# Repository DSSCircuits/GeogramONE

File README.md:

The Geogram ONE is an open source tracking device/development board based off the Arduino platform.

The hardware design and software files are released under CC-SA v3 license.

There are several attributable portions of code that will be listed shortly.

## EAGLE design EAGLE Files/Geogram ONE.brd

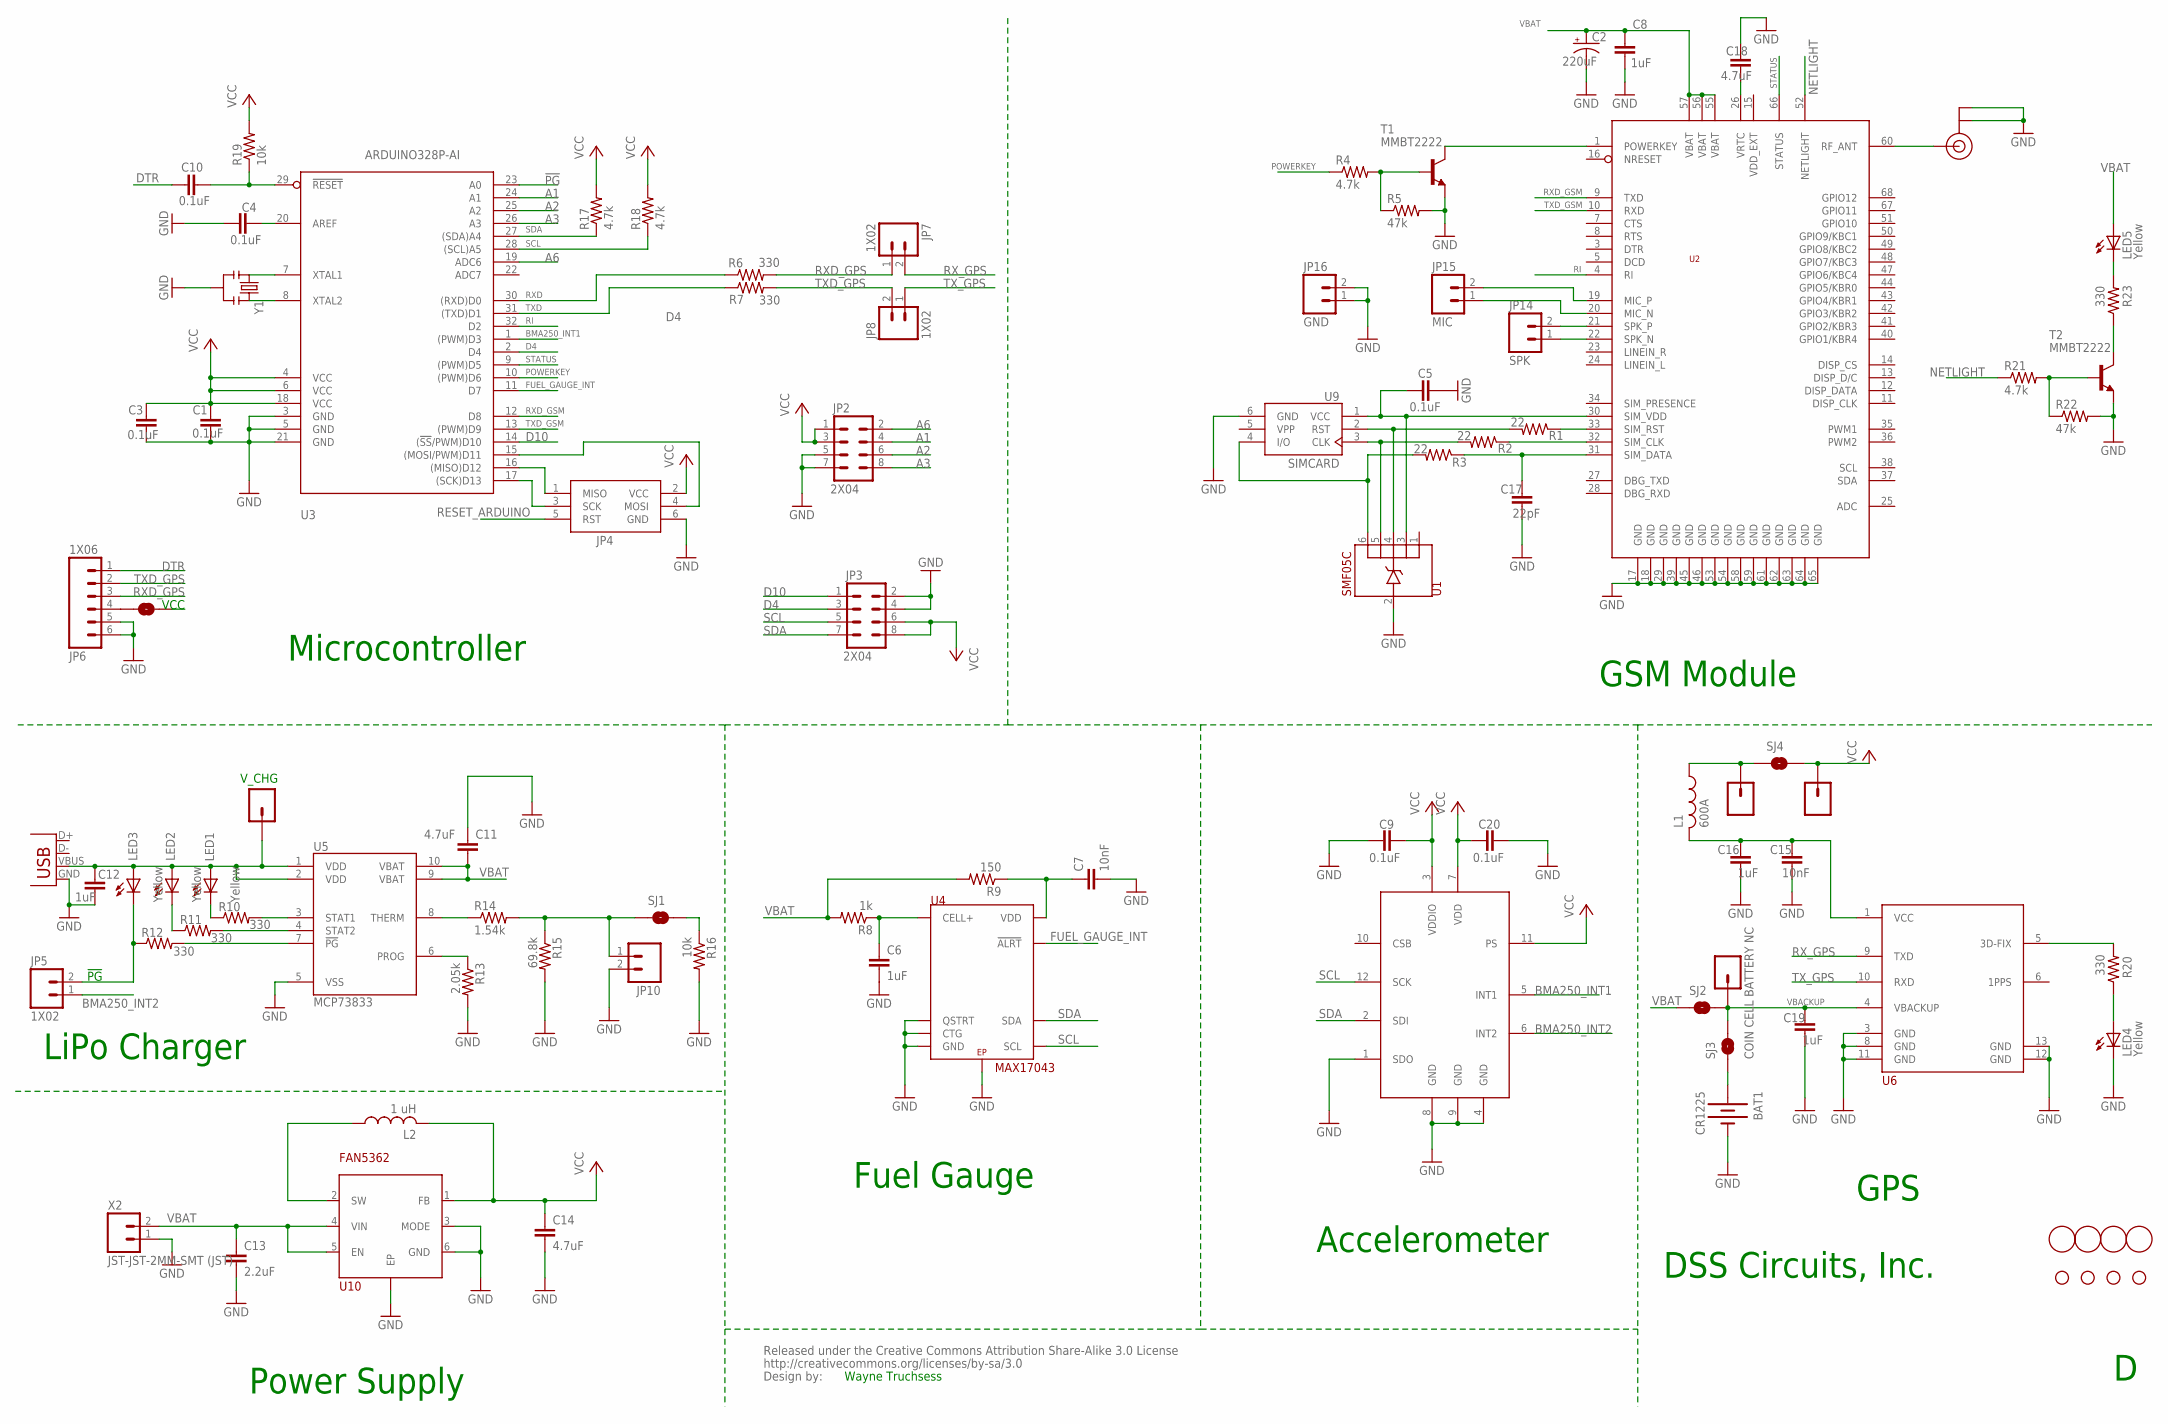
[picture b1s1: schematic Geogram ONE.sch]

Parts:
BAT1: CR1225; BATTCON_12MM; MOUSER# 534-3000TR; DIGIKEY# 3000KTR-ND
C1, C3, C4, C5, C9, C10, C20: 0.1uF; C0603; MOUSER# 80-C0603C104K8R; DIGIKEY# 399-1095-2-ND
C2: 220uF; D/7343-31R; MOUSER# 80-T520D227M010; DIGIKEY# 399-4045-2-ND
C6, C8, C12, C16, C19: 1uF; C0603; MOUSER# 810-C1608X5R1A105K; DIGIKEY# 445-1321-2-ND
C7, C15: 10nF; C0603; MOUSER# 77-VJ0603Y103KXQCBC
C11, C14, C18: 4.7uF; C0603; MOUSER# 80-C0603C475K9P; DIGIKEY# 399-3482-2-ND
C13: 2.2uF; C0603; MOUSER# 80-C0603C225K9P; DIGIKEY# 399-3362-2-ND
C17: 22pF; C0603; MOUSER# 77-VJ0603A220KXJPBC
FIDUCIAL1, FIDUCIAL2, FIDUCIAL3, FIDUCIAL4: FIDUCIAL; FIDUCIAL_1MM
JP2, JP3: 2X04; 2X4
JP4: AVRISP-6; AVRISP
JP5, JP7, JP8: 1X02; 1X02_NO_SILK
JP6: 1X06
JP9: V_CHG; 1X01
JP10: EXT THERMISTER; 1X02_NO_SILK
JP11: EXT_BAT; 1X01
JP12, JP13: EXT GPS POWER JPR; 1X01
JP14: SPK; 1X02_NO_SILK
JP15: MIC; 1X02_NO_SILK
JP16: GND; 1X02_NO_SILK
L1: 600A; L2012C; MOUSER# 810-MMZ2012R601A
L2: 1 uH; L2012C; MOUSER# 81-LQM21PN1R0MC0D; DIGIKEY# 490-4992-2-ND
LED1, LED2, LED3, LED4, LED5: Yellow; CHIP-LED0603; MOUSER# 720-LYQ971H1K136; DIGIKEY# 475-2557-2-ND
LICENSE: CREATIVE_COMMONS
R1, R2, R3: 22; R0603; MOUSER# 667-ERJ-3EKF22R0V; DIGIKEY# P22.0HTR-ND
R4, R17, R18, R21: 4.7k; R0603; MOUSER# 667-ERJ-3EKF4701V; DIGIKEY# P4.70KHTR-ND
R5, R22: 47k; R0603; MOUSER# 667-ERJ-3EKF4702V; DIGIKEY# P47.0KHTR-ND
R6, R7, R10, R11, R12, R20, R23: 330; R0603; MOUSER# 667-ERJ-3EKF3300V; DIGIKEY# P330HTR-ND
R8: 1k; R0603; MOUSER# 667-ERJ-3EKF1001V; DIGIKEY# P1.00KHTR-ND
R9: 150; R0603; MOUSER# 667-ERJ-3EKF1500V; DIGIKEY# P150HTR-ND
R13: 2.05k; R0603; MOUSER# 667-ERJ-3EKF2051V; DIGIKEY# P2.05KHTR-ND
R14: 1.54k; R0603; MOUSER# 71-CRCW0603-1.54K-E3; DIGIKEY# 541-1.54KHTR-ND
R15: 69.8k; R0603; MOUSER# 667-ERJ-3EKF6982V; DIGIKEY# P69.8KHTR-ND
R16, R19: 10k; R0603; MOUSER# 667-ERJ-3EKF1002V; DIGIKEY# P10.0KHTR-ND
SJ1: EXT THERMISTER NC; SJ_2S-TRACE
SJ2: LIPO BATTERY NO; SJ_2S-NO
SJ3: COIN CELL BATTERY NC; SJ_2S-TRACE
SJ4: EXT GPS POWER NC; SJ_2S-TRACE
SJ5: EXT VCC NO; SJ_2S-NO
STANDOFF1, STANDOFF2, STANDOFF3, STANDOFF4: STAND-OFF
T1, T2: MMBT2222; SOT23-BEC; MOUSER# 512-MMBT2222A; DIGIKEY# MMBT2222AFSTR-ND
U1: SMF05C; SC70-6L; DIGIKEY# SMF05CTR-ND
U2: SIM900
U3: ARDUINO328P-AI; TQFP32-08; MOUSER# 556-ATMEGA328P-AU; DIGIKEY# ATMEGA328P-AU-ND
U4: MAX17043; TDFN8; MOUSER# 700-MAX17043G+T; DIGIKEY# MAX17043G+T-ND
U5: MCP73833; MSOP-10; MOUSER# 579-MCP73833-FCI/UN; DIGIKEY# MCP73833-FCI/UN-ND
U6: PA6C
U7: BMA250; 12LGA_VGG3-D; DIGIKEY# 828-1023-6-ND
U8: U.FL; MOUSER# 960-RECE20279001E01; DIGIKEY# 931-1107-2-ND
U9: SIMCARD; MOUSER# 649-7111S2015X02LF; DIGIKEY# 609-1401-2-ND
U10: FAN5362; UMLP; MOUSER# 512-FAN5362UMP33X; DIGIKEY# FAN5362UMP33X-ND
X1: USBSMD; USB-MINIB; DIGIKEY# ED2992TR-ND
X2: JST-JST-2MM-SMT (JST); JST; DIGIKEY# 455-1749-2-ND
Y1: 8 MHz; RESONATOR-SMD; MOUSER# 81-CSTCE8M00G52Z-R0

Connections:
!PG: JP5.2, LED3.C, R12.1, U3.23 (A0)
A1: JP2.4, U3.24 (A1)
A2: JP2.6, U3.25 (A2)
A3: JP2.8, U3.26 (A3)
A6: JP2.2, U3.19 (ADC6)
AREF: C4.2, U3.20 (AREF)
BMA250_INT1: U3.1 ((PWM)D3), U7.5 (INT1)
BMA250_INT2: JP5.1, U7.6 (INT2)
D4: JP3.3, U3.2 (D4)
D10: JP3.1, U3.14 ((!SS!/PWM)D10)
DTR: C10.1, JP6.1
FUEL_GAUGE_INT: U3.11 (D7), U4.!ALRT
GND: BAT1.GND (-), C1.2, C2.-, C3.2, C4.1, C5.2, C6.2, C7.2, C8.2, C9.2, C11.1, C12.2, C13.2, C14.2, C15.1, C16.1, C17.1, C18.1, C19.1, C20.1, JP2.5, JP2.7, JP3.2, JP3.4, JP4.6 (GND), JP6.5, JP6.6, JP10.2, JP16.1, JP16.2, LED4.C, R5.2, R13.2, R15.2, R16.2, R22.2, T1.E, T2.E, U1.2, U2.17 (GND), U2.18 (GND), U2.29 (GND), U2.39 (GND), U2.45 (GND), U2.46 (GND), U2.53 (GND), U2.54 (GND), U2.58 (GND), U2.59 (GND), U2.61 (GND), U2.62 (GND), U2.63 (GND), U2.64 (GND), U2.65 (GND), U3.3 (GND), U3.5 (GND), U3.21 (GND), U4.CTG, U4.EP, U4.GND, U4.QSTRT, U5.5 (VSS), U6.3 (GND), U6.8 (GND), U6.11 (GND), U6.12 (GND), U6.13 (GND), U7.1 (SDO), U7.4 (GND), U7.8 (GND), U7.9 (GND), U8.P$1 (GND), U8.P$2 (GND), U9.6 (GND), U10.3 (MODE), U10.6 (GND), U10.7 (EP), X1.GND, X2.1, Y1.2
MIC_N: JP15.1, U2.20 (MIC_N)
MIC_P: JP15.2, U2.19 (MIC_P)
MISO: JP4.1 (MISO), U3.16 ((MISO)D12)
MOSI: JP4.4 (MOSI), U3.15 ((MOSI/PWM)D11)
unnamed: C18.2, U2.26 (VRTC)
unnamed: R2.1, U2.32 (SIM_CLK)
unnamed: R20.2, U6.5 (3D-FIX)
unnamed: C6.1, R8.1, U4.CELL+
unnamed: R1.1, U2.33 (SIM_RST)
unnamed: C17.2, R3.1, U2.31 (SIM_DATA)
unnamed: R2.2, U1.5, U9.3 (CLK)
unnamed: R1.2, U1.4, U9.2 (RST)
unnamed: R3.2, U1.6, U9.4 (I/O)
unnamed: LED4.A, R20.1
unnamed: U2.60 (RF_ANT), U8.P$3 (SIGNAL)
unnamed: T1.C, U2.1 (POWERKEY)
unnamed: R4.2, R5.1, T1.B
unnamed: BAT1.PWR@2 (+), SJ3.1
unnamed: R21.2, R22.1, T2.B
unnamed: R23.1, T2.C
unnamed: JP6.4, SJ5.2
unnamed: C7.1, R9.1, U4.VDD
unnamed: LED1.C, R10.1
unnamed: LED2.C, R11.1
unnamed: JP12.1, L1.1, SJ4.1, SJ5.1
unnamed: R13.1, U5.6 (PROG)
unnamed: R14.1, U5.8 (THERM)
unnamed: LED5.C, R23.2
unnamed: JP10.1, R14.2, R15.1, SJ1.1
unnamed: L2.1, U10.2 (SW)
unnamed: R16.1, SJ1.2
NETLIGHT: R21.1, U2.52 (NETLIGHT)
PG: R12.2, U5.7 (!PG)
POWERKEY: R4.1, U3.10 ((PWM)D6)
RESET_ARDUINO: C10.2, JP4.5 (RST), R19.1, U3.29 (!RESET)
RI: U2.4 (RI), U3.32 (D2)
RXD: R6.1, U3.30 ((RXD)D0)
RXD_GPS: JP6.3, JP7.1, R6.2
RXD_GSM: U2.9 (TXD), U3.12 (D8)
RX_GPS: JP7.2, U6.9 (TXD)
SCK: JP4.3 (SCK), U3.17 ((SCK)D13)
SCL: JP3.5, R18.1, U3.28 ((SCL)A5), U4.SCL, U7.12 (SCK)
SDA: JP3.7, R17.1, U3.27 ((SDA)A4), U4.SDA, U7.2 (SDI)
SIM_VDD: C5.1, U1.3, U2.30 (SIM_VDD), U9.1 (VCC)
SPK_N: JP14.1, U2.22 (SPK_N)
SPK_P: JP14.2, U2.21 (SPK_P)
STAT1: R10.2, U5.3 (STAT1)
STAT2: R11.2, U5.4 (STAT2)
STATUS: U2.66 (STATUS), U3.9 ((PWM)D5)
TXD: R7.1, U3.31 ((TXD)D1)
TXD_GPS: JP6.2, JP8.2, R7.2
TXD_GSM: U2.10 (RXD), U3.13 ((PWM)D9)
TX_GPS: JP8.1, U6.10 (RXD)
VBACKUP: C19.2, JP11.1, SJ2.2, SJ3.2, U6.4 (VBACKUP)
VBAT: C2.+, C8.1, C11.2, C13.1, LED5.A, R8.2, R9.2, SJ2.1, U2.55 (VBAT), U2.56 (VBAT), U2.57 (VBAT), U5.9 (VBAT), U5.10 (VBAT), U10.4 (VIN), U10.5 (EN), X2.2
VBUS: C12.1, JP9.1, LED1.A, LED2.A, LED3.A, U5.1 (VDD), U5.2 (VDD), X1.VBUS
VCC: C1.1, C3.1, C9.1, C14.1, C20.2, JP2.1, JP2.3, JP3.6, JP3.8, JP4.2 (VCC), JP13.1, L2.2, R17.2, R18.2, R19.2, SJ4.2, U3.4 (VCC), U3.6 (VCC), U3.18 (VCC), U7.3 (VDDIO), U7.7 (VDD), U7.11 (PS), U10.1 (FB)
VCC_GPS: C15.2, C16.2, L1.2, U6.1 (VCC)
VDD_EXT: U2.15 (VDD_EXT)
VPP: U9.5 (VPP)
XTAL1: U3.7 (XTAL1), Y1.1
XTAL2: U3.8 (XTAL2), Y1.3

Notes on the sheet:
Microcontroller
GSM Module
GPS
Fuel Gauge
Accelerometer
Power Supply
LiPo Charger
V_CHG
DSS Circuits, Inc.
VCC
!PG
Wayne Truchsess

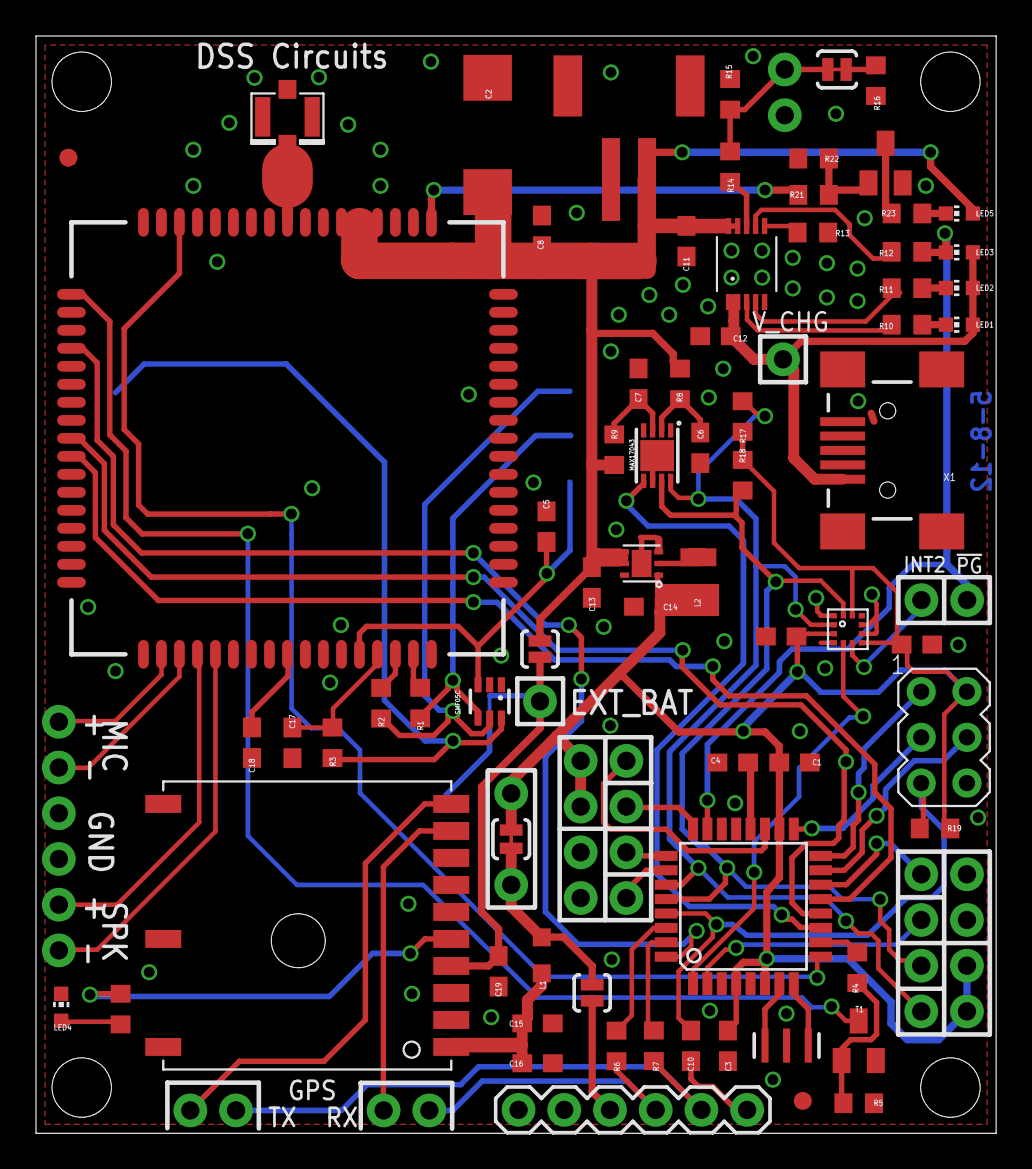
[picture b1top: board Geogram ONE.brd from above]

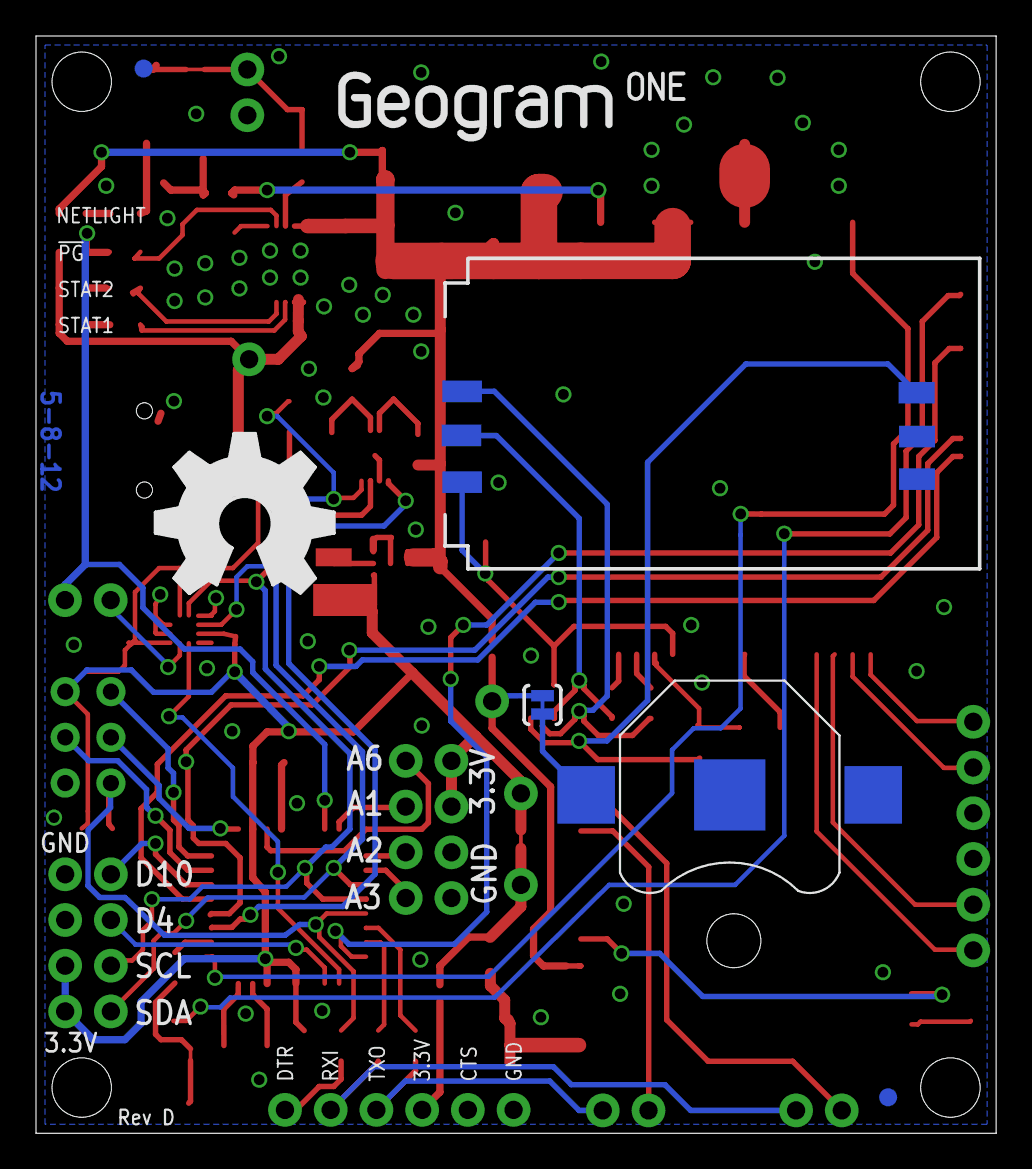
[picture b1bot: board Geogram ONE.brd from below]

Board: 2 copper layers, 53.3 x 61.0 mm, 97 parts (7 on the bottom side), 73 nets.

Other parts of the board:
U$10: OSHW_FILLX350_NOTEXT
U$11: GEOGRAM_ONE_LOGO

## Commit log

2012-09-10 Fixed PositionFixIndicator reference. Modified algorithms for geofences
2012-09-10 First commit of README.md
2012-09-10 Added beta release of EEPROM Map (unfinished) Converting #define configuration constants to EEPROM settings
2012-09-10 changes to fence algorithm added delay to GPS sentence collection to disregard GPVTG sentence added serial.available check before calling GPS data collection
2012-09-10 see previous commit comments
2012-09-14 removed references to EEPROM removed interrupt specific functions and switched to generic functions
2012-09-14 added more EEPROM settings
2012-09-14 added functions to configure variables from EEPROM
2012-09-14 removed EEPROM references
2012-09-14 no changes
2012-09-14 added EEPROM configuration function
2012-09-14 added EEPROM configuration function calls
2012-09-14 changed function calls to BMA250
2012-09-14 changed fence function call names
2012-09-14 changed function call names
2012-10-01 Updated address map
2012-10-01 - Fixed analogRead addressing - Updates to sleep configuration - Updates to fence configuration
2012-10-01 - Added more EEPROM references
2012-10-01 - Added capability to IO pins
2012-10-01 - Updated fence calculations
2012-10-01 - changed fence latitude and longitudes to longs from floats
2012-10-01 - Added sleepmode function call to power down function call
2012-10-01 - Added functionality for different date formats - Added functionality for listing geo data or using http google maps link
2012-10-01 - Added option to leave motion interrupts enables if sleep config enabled
2012-10-01 - Updated fence calculations after changing from float to long
2012-10-01 - Updated function call to use global variables
2012-10-01 - Function now saves value to EEPROM
2012-10-01 - rewrite of sleep timer function
2012-10-01 - Updated EEPROM maps
2012-10-01 - Included EEPROM readAnything template
2012-10-01 - Updated charger status algorithm
2012-10-01 - Updated function call to use global variable
2012-10-01 - Updated global variables - Updated geofence calculations - Updated sleep timer calculations
2012-10-15 -House keeping
2012-10-15 - House keeping
2012-10-15 - Added additional registers to configuration
2012-10-15 - Added option for user programmable parameters for display
2012-10-15 - Changed return type to void
2012-10-15 - Updated offsets to reflect EEPROM map change
2012-10-15 - changed return type to void - updated to use messages from EEPROM
2012-10-15 - changed return type to void - updates to reflect changes to EEPROM map
2012-10-15 - Added interrupt routines for D4 and D10 pin change interrupts
2012-10-15 - Added support for pin change interrupts
2012-10-15 - New EEPROM map
2012-10-15 - updates to reflect new EEPROM map - removed some unnecessary function calls
2012-10-19 - fixed but in longitude and latitude calculation
2012-11-09 Small change to display format
2012-11-11 -fixed bug affecting operation in positive (UTC +) timezones
2012-11-16 - Fixed bug associated with latitude and/or longitude readings being off when degrees was less than zero
    - Changed BYTE declaration in SIM900.cpp to char to allow compilation in Arduino 1.0 and above
2012-12-13 Fixed bug with battery voltage being reported incorrectly
2012-12-13 Removed debugging print statements that were left in
2013-01-10 Complete rewrite
2013-01-11 beta
2013-01-11 beta2
2013-01-12 update. just before rewrite of atcommand
2013-01-13 another update and it's not working
2013-01-13 Working beta with code optimized.
2013-03-02 part of rewrite
2013-04-12 more changes
2013-04-13 trying new AT command function
2013-04-14 more changes, this setup works but need to get rid of all the errors and streamline the process more.
2013-05-05 -including PA6C rewrite
2013-05-07 - fixed issue with smspending
2013-05-09 - works. Getting ready to rewrite PA6C library to use character arrays instead of longs and floats
2013-06-05 updated map
2013-06-05 EEPROM files
2013-06-05 added EEPROM files
2013-06-05 cleaned up files
2013-06-06 changed BYTE reference to char to make compatible with Arduino 1.0 and above.
2013-06-07 added ELSE statement to recover from error during CIPSEND
2013-06-09 - fixed BYTE references in EEPROM files to support compiling in Arduino 1.0 and above
2013-06-09 - fixed another BYTE reference for Arduino 1.0 compatibility
2013-06-13 -added support to reattach to GPRS network if it detects it's detached
2013-06-13 - added option to check for gsm signal before trying to attach to GPRS service
2013-06-14 - added option to reboot GSM module every 5 minutes if GPRS connection can not be reattached. According to documentation, in worst case scenario a reboot may be necessary.
2013-06-14 break from recovery if not registered to network
2013-06-15 - added Option 255 which is used to reboot GSM module remotely - added 2 second delay after GSM power down in UDP recovery because of inconsistency issues powering back on
2013-06-18 Attempting to add HTTP requests
    This is not working, this is still a work in progress.
2013-06-18 moved code around added comments
2013-06-19 http get request
    Got farther but still having errors
2013-06-20 Got call home working with HTTP POST
2013-06-22 Working example
    Got everything work, removed all old code started on comments and help
    files. renamed pde to ino for new arduino. included google maps php file
2013-06-24 fixed bug with GPS check
    GPS is more correct and updates more often.
2013-07-05 -changed udp function to uint8_t from void and moved some parameters to the main loop.
2013-07-08 - updated EEPROM map - changed format to give the option to program the EEPROM or just read the memory contents
2013-07-08 - added a flag for monitoring the GSM power status
2013-07-08 - added functionality for send intervals for sms and udp based off charger, motion and speed status
2013-07-08 - added functionality for send intervals for sms and udp based off charger, motion and speed status - added support to poll the GSM at the end of each loop to verify device is still powered on. If it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
2013-07-08 - added functionality for send intervals for sms and udp based off charger, motion and speed status - accelerometer interrupts will be enabled all the time now.
2013-07-12 - Added support for different power profiles for send intervals with SMS and UDP. You can set different intervals for plugged in/charging and on battery. You can also program overrides for profile wi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
    - Fixed bug with Geofences
    - Updated EEPROM map to reflect new settings. If using this version you will need to reprogram the EEPROM also
    - Upda
2013-07-13 - beta testing a new functionality for those encasing the GO's and looking for a way to power it on and off. First enable the power switch by setting #define USEPOWERSWITCH to a 1. Next connect a pus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
2013-07-14 Updated and merged with GeoGramOne
    Updated and merged with GeoGramOne latest code
2013-07-20 - removed unnecessary files
2014-07-20 added function BMA250sleepMode to enable sleep mode
2014-07-20 combined sleep and wake functions
2014-07-20 changed function return types to void modified algorithms to clean up code
2014-07-20 code cleanup
2014-07-20 added support for sending emails along with SMS added function to get IMEI number using AT commands added function to reboot GSM changed smsCmdString from 30 to 70 to fix bug with certain incoming sm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
2014-07-20 included #define for APN in email support feature modified sleep function by adding passed parameters to choose sleepmode, give the option to backup the pin change interrupt register and disable AltS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
2014-07-20 modified EEPROM map to reflect changes in functionality
2014-07-20 include #define APN for email support changed default PINCODE to 0000 changed default GeoID to display firmware version changed default http2 from "+(" to " (" due to problem with updates in Google M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
2014-07-20 code cleanup to include GSM reboot function added code to automatically populate the IMEI EEPROM field if IMEI[0] contains a space enabled ability to send number of satellites used in UDP string
2014-07-20 enabled use of USEPOWERSWITCH for pin D11 included support for email functionality included function call to reconfigure accelerometer motion settings. Can be used when tweaking accelerometer sensiti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
2014-07-20 added new functionality for Power on Tracking Only. PoTO is enabled when bit 3 is true in sleepTimeConfig. changed the call from init to initializeGSM on wake up
2014-07-20 code cleanup to reflect changes in goesWhere function
2014-07-20 included ability to put MAX17043 in sleep mode to reduce power consumption included ability to put accelerometer in sleep mode to reduce power consumption changed the option to only send message to a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
2014-07-20 changed option to only send messages to address stored in EEPROM
2014-07-20 added variable to APN to list changed terminating delimiting character to a colon from period to fix problems when certain fields required the use of a period being stored. See exceptions below: exce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
2014-07-20 code change to reflect changes to goesWhere to keep outgoing message sent to address configuration stored in EEPROM added ability to pulse the pin for a programmable amount of time
2014-07-20 changed file name

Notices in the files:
parts and their libraries:
SparkFun: Released under the Creative Commons Attribution Share-Alike 3.0 License
SparkFun: http://creativecommons.org/licenses/by-sa/3.0
